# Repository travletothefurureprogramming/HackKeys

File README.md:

# HackKeys
HackKeys is a custom macropad designed for programmers who want to speed up their workflow. With fully programmable keys, HackKeys lets you assign shortcuts and trigger commands with a single press. It’s both functional and customizable. Whether you’re coding, or managing tools, HackKey helps you stay efficient and creative at the keyboard.

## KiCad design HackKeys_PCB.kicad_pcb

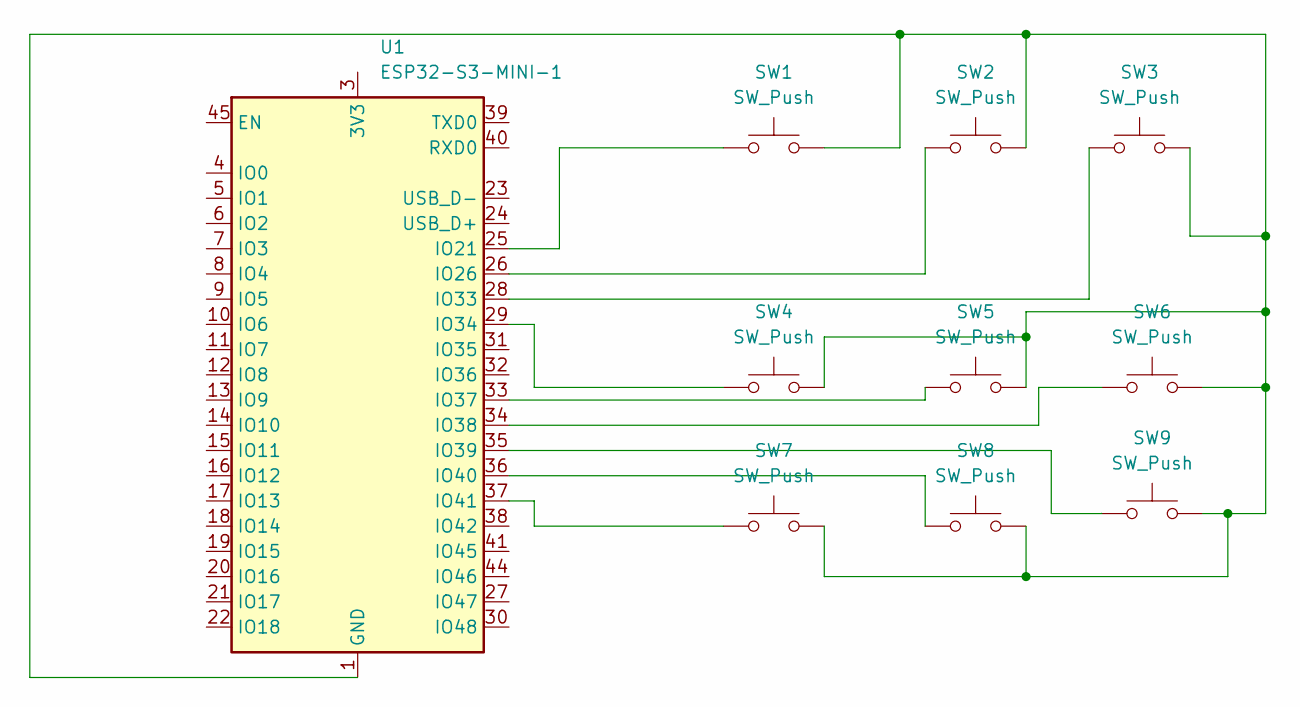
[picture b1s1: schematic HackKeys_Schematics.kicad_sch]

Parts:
SW1, SW2, SW3, SW4, SW5, SW6, SW7, SW8, SW9: SW_Push; SW_Cherry_MX_1.00u_PCB
U1: ESP32-S3-MINI-1; ESP32-S2-MINI-1

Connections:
unnamed: SW1.2, SW2.2, SW3.2, SW4.2, SW5.2, SW6.2, SW7.2, SW8.2, SW9.2, U1.1 (GND), U1.2 (GND), U1.42 (GND), U1.43 (GND), U1.46 (GND), U1.47 (GND), U1.48 (GND), U1.49 (GND), U1.50 (GND), U1.51 (GND), U1.52 (GND), U1.53 (GND), U1.54 (GND), U1.55 (GND), U1.56 (GND), U1.57 (GND), U1.58 (GND), U1.59 (GND), U1.60 (GND), U1.61 (GND), U1.62 (GND), U1.63 (GND), U1.64 (GND), U1.65 (GND)
unnamed: SW1.1, U1.25 (IO21)
unnamed: SW2.1, U1.26 (IO26)
unnamed: SW3.1, U1.28 (IO33)
unnamed: SW4.1, U1.29 (IO34)
unnamed: SW5.1, U1.33 (IO37)
unnamed: SW6.1, U1.34 (IO38)
unnamed: SW9.1, U1.35 (IO39)
unnamed: SW8.1, U1.36 (IO40)
unnamed: SW7.1, U1.37 (IO41)

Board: 2 copper layers, 10 parts (0 on the bottom side), 10 nets, no tracks yet.
